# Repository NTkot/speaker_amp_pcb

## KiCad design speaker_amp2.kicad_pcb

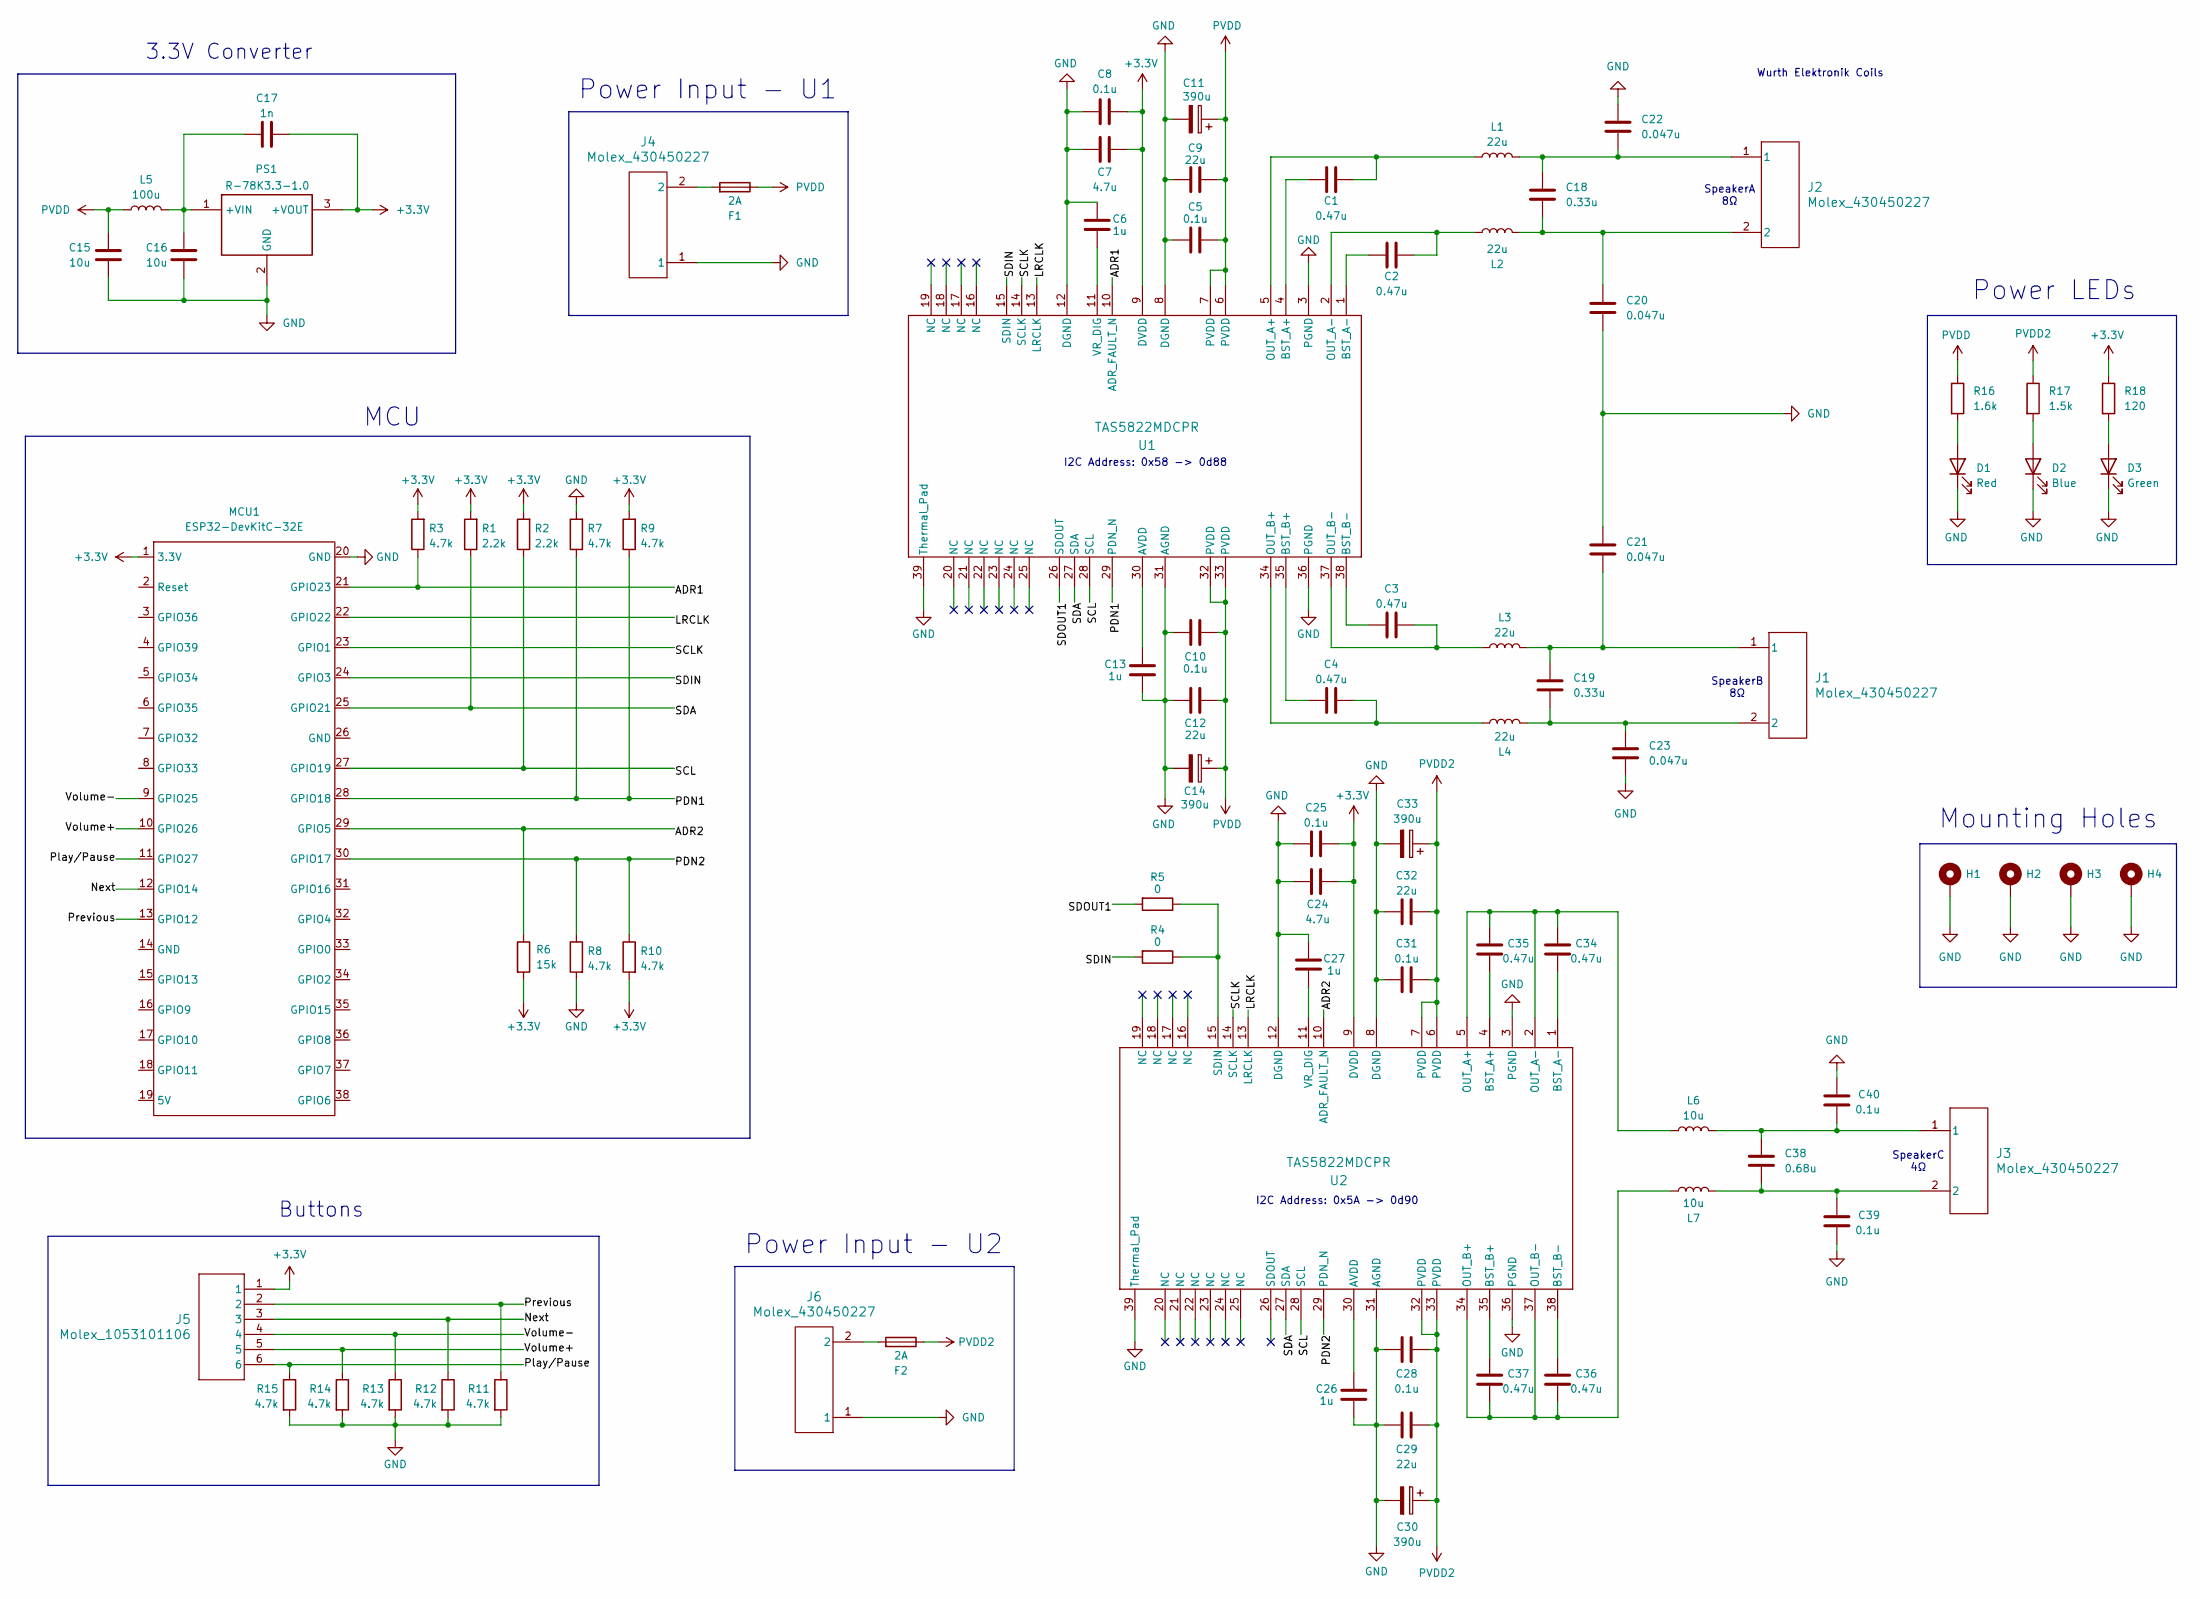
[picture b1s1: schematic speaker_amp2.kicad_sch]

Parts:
C1, C2, C3, C4, C34, C35, C36, C37: 0.47u; C_0603_1608Metric_Pad1.08x0.95mm_HandSolder
C5, C8, C10, C25, C28, C31: 0.1u; C_0603_1608Metric_Pad1.08x0.95mm_HandSolder
C6, C13, C26, C27: 1u; C_0603_1608Metric_Pad1.08x0.95mm_HandSolder
C7, C24: 4.7u; C_0805_2012Metric_Pad1.18x1.45mm_HandSolder
C9, C12, C29, C32: 22u; C_0805_2012Metric_Pad1.18x1.45mm_HandSolder
C11, C14, C30, C33: 390u; CP_Radial_D8.0mm_P3.50mm
C15, C16: 10u; C_0805_2012Metric_Pad1.18x1.45mm_HandSolder
C17: 1n; C_0805_2012Metric_Pad1.18x1.45mm_HandSolder
C18, C19: 0.33u; C_2824
C20, C21, C22, C23: 0.047u; C_2220_5750Metric_Pad1.97x5.40mm_HandSolder
C38: 0.68u; C_2220_5750Metric_Pad1.97x5.40mm_HandSolder
C39, C40: 0.1u; C_2220_5750Metric_Pad1.97x5.40mm_HandSolder
D1: Red; LED_PLCC-2_3.4x3.0mm_KA
D2: Blue; LED_PLCC-2_3.4x3.0mm_KA
D3: Green; LED_PLCC-2_3.4x3.0mm_KA
F1, F2: 2A; Fuse_1206_3216Metric
H1, H2, H3, H4: MountingHole_Pad; MountingHole_3.2mm_M3_DIN965_Pad_TopBottom
J1, J2, J3, J4, J6: Molex_430450227; 430450227_MOLEX
J5: Molex_1053101106
L1, L2, L3, L4: 22u; WE_7447773220
L5: 100u; RLS186
L6, L7: 10u; L_Wuerth_WE-PDF_Handsoldering_7mm_apart
MCU1: ESP32-DevKitC-32E
PS1: R-78K3.3-1.0; R78K3310
R1, R2: 2.2k; R_0805_2012Metric_Pad1.20x1.40mm_HandSolder
R3, R7, R8, R9, R10, R11, R12, R13, R14, R15: 4.7k; R_0805_2012Metric_Pad1.20x1.40mm_HandSolder
R4, R5: 0; R_0805_2012Metric_Pad1.20x1.40mm_HandSolder
R6: 15k; R_0805_2012Metric_Pad1.20x1.40mm_HandSolder
R16: 1.6k; R_0805_2012Metric_Pad1.20x1.40mm_HandSolder
R17: 1.5k; R_0805_2012Metric_Pad1.20x1.40mm_HandSolder
R18: 120; R_0805_2012Metric_Pad1.20x1.40mm_HandSolder
U1, U2: TAS5822MDCPR; DCP0038A-IPC_C

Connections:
+3.3V: C7.1, C8.1, C17.1, C24.2, C25.1, J5.1, MCU1.1 (3.3V), PS1.3 (+VOUT), R1.2, R2.2, R3.2, R6.2, R9.2, R10.2, R18.1, U1.9 (DVDD), U2.9 (DVDD)
/ADR1: MCU1.21 (GPIO23), R3.1, U1.10 (ADR_FAULT_N)
/ADR2: MCU1.29 (GPIO5), R6.1, U2.10 (ADR_FAULT_N)
/LRCLK: MCU1.22 (GPIO22), U1.13 (LRCLK), U2.13 (LRCLK)
/Next: J5.3, MCU1.12 (GPIO14), R12.1
/PDN1: MCU1.28 (GPIO18), R7.1, R9.1, U1.29 (PDN_N)
/PDN2: MCU1.30 (GPIO17), R8.1, R10.1, U2.29 (PDN_N)
/Play/Pause: J5.6, MCU1.11 (GPIO27), R15.1
/Previous: J5.2, MCU1.13 (GPIO12), R11.1
/SCL: MCU1.27 (GPIO19), R2.1, U1.28 (SCL), U2.28 (SCL)
/SCLK: MCU1.23 (GPIO1), U1.14 (SCLK), U2.14 (SCLK)
/SDA: MCU1.25 (GPIO21), R1.1, U1.27 (SDA), U2.27 (SDA)
/SDIN: MCU1.24 (GPIO3), R4.2, U1.15 (SDIN)
/SDOUT1: R5.2, U1.26 (SDOUT)
/Volume+: J5.5, MCU1.10 (GPIO26), R14.1
/Volume-: J5.4, MCU1.9 (GPIO25), R13.1
GND: C5.1, C6.2, C7.2, C8.2, C9.1, C10.1, C11.2, C12.1, C13.1, C14.2, C15.1, C16.1, C20.2, C21.1, C22.1, C23.2, C24.1, C25.2, C26.1, C27.1, C28.2, C29.2, C30.2, C31.2, C32.2, C33.2, C39.1, C40.2, D1.1 (K), D2.1 (K), D3.1 (K), H1.1, H2.1, H3.1, H4.1, J4.1, J6.1, MCU1.20 (GND), PS1.2 (GND), R7.2, R8.2, R11.2, R12.2, R13.2, R14.2, R15.2, U1.3 (PGND), U1.8 (DGND), U1.12 (DGND), U1.31 (AGND), U1.36 (PGND), U1.39 (Thermal_Pad), U2.3 (PGND), U2.8 (DGND), U2.12 (DGND), U2.31 (AGND), U2.36 (PGND), U2.39 (Thermal_Pad)
unnamed: C18.1, C22.2, J2.1, L1.2
unnamed: C18.2, C20.1, J2.2, L2.2
unnamed: C19.1, C21.2, J1.1, L3.2
unnamed: C19.2, C23.1, J1.2, L4.2
unnamed: C38.1, C40.1, J3.1, L6.2
unnamed: C38.2, C39.2, J3.2, L7.2
unnamed: D1.2 (A), R16.2
unnamed: D2.2 (A), R17.2
unnamed: D3.2 (A), R18.2
unnamed: F1.2, J4.2
unnamed: F2.2, J6.2
unnamed: C16.2, C17.2, L5.2, PS1.1 (+VIN)
unnamed: C13.2, U1.30 (AVDD)
unnamed: C1.1, U1.4 (BST_A+)
unnamed: C2.1, U1.1 (BST_A-)
unnamed: C4.1, U1.35 (BST_B+)
unnamed: C3.1, U1.38 (BST_B-)
unnamed: C1.2, L1.1, U1.5 (OUT_A+)
unnamed: C2.2, L2.1, U1.2 (OUT_A-)
unnamed: C4.2, L4.1, U1.34 (OUT_B+)
unnamed: C3.2, L3.1, U1.37 (OUT_B-)
unnamed: C6.1, U1.11 (VR_DIG)
unnamed: C26.2, U2.30 (AVDD)
unnamed: C35.1, U2.4 (BST_A+)
unnamed: C34.1, U2.1 (BST_A-)
unnamed: C37.2, U2.35 (BST_B+)
unnamed: C36.2, U2.38 (BST_B-)
unnamed: C34.2, C35.2, L6.1, U2.2 (OUT_A-), U2.5 (OUT_A+)
unnamed: C36.1, C37.1, L7.1, U2.34 (OUT_B+), U2.37 (OUT_B-)
unnamed: R4.1, R5.1, U2.15 (SDIN)
unnamed: C27.2, U2.11 (VR_DIG)
PVDD: C5.2, C9.2, C10.2, C11.1, C12.2, C14.1, C15.2, F1.1, L5.1, R16.1, U1.6 (PVDD), U1.7 (PVDD), U1.32 (PVDD), U1.33 (PVDD)
PVDD2: C28.1, C29.1, C30.1, C31.1, C32.1, C33.1, F2.1, R17.1, U2.6 (PVDD), U2.7 (PVDD), U2.32 (PVDD), U2.33 (PVDD)

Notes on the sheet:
Wurth Elektronik Coils
Power Input - U2
MCU
SpeakerC 4Ω
SpeakerA 8Ω
I2C Address: 0x58 -> 0d88
I2C Address: 0x5A -> 0d90
Power LEDs
SpeakerB 8Ω
Buttons
Mounting Holes
3.3V Converter
Power Input - U1

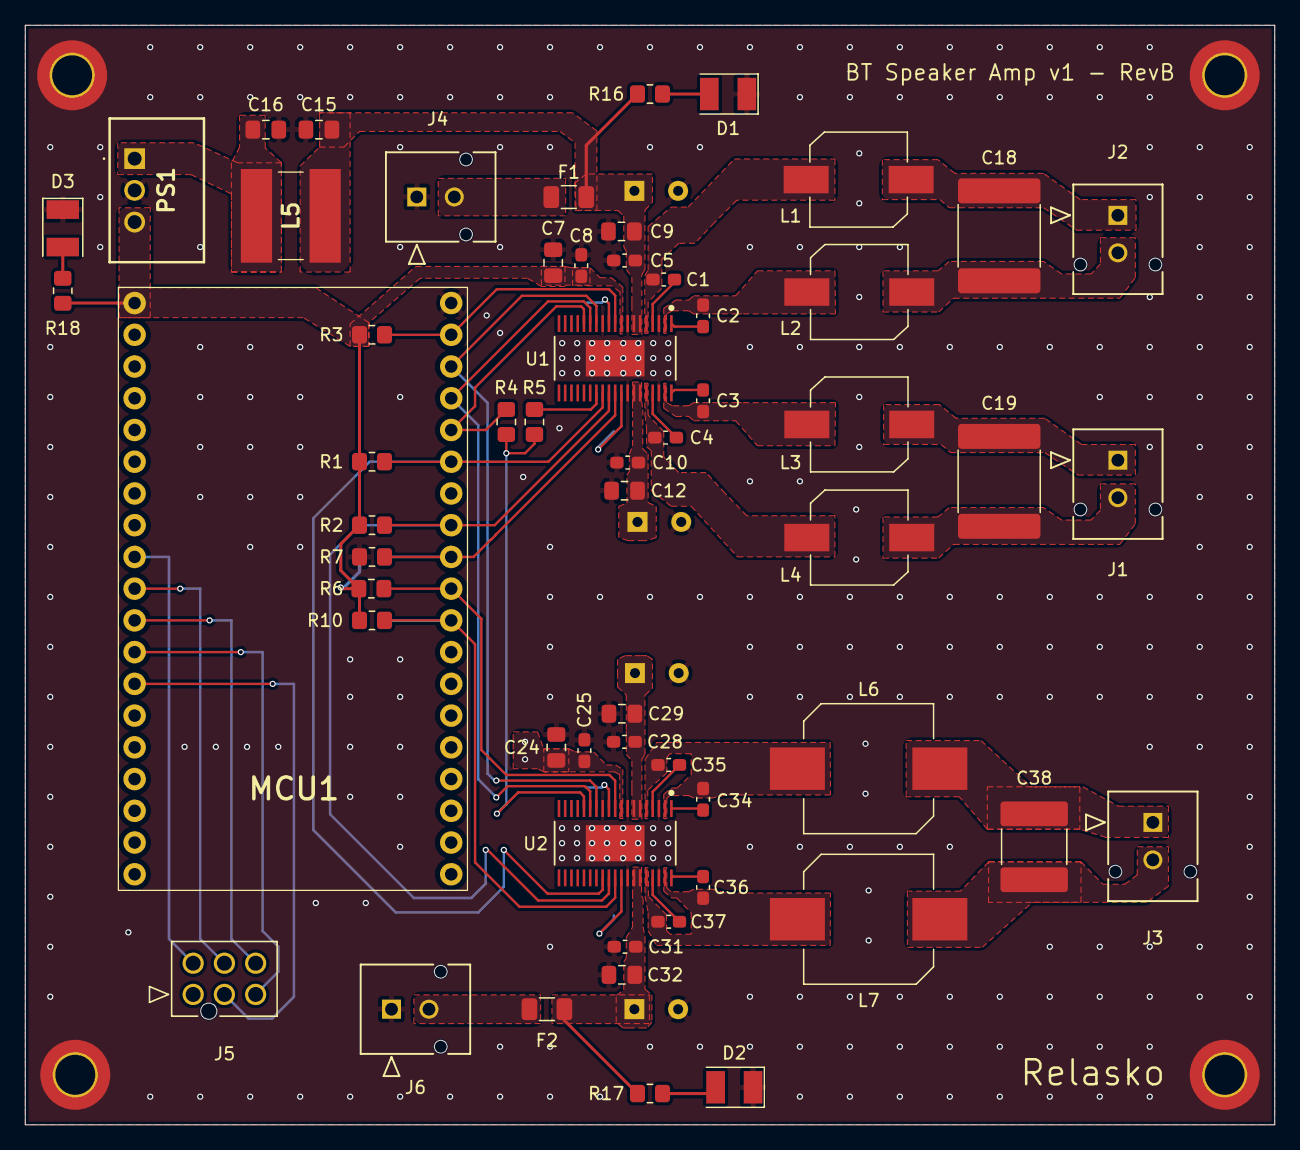
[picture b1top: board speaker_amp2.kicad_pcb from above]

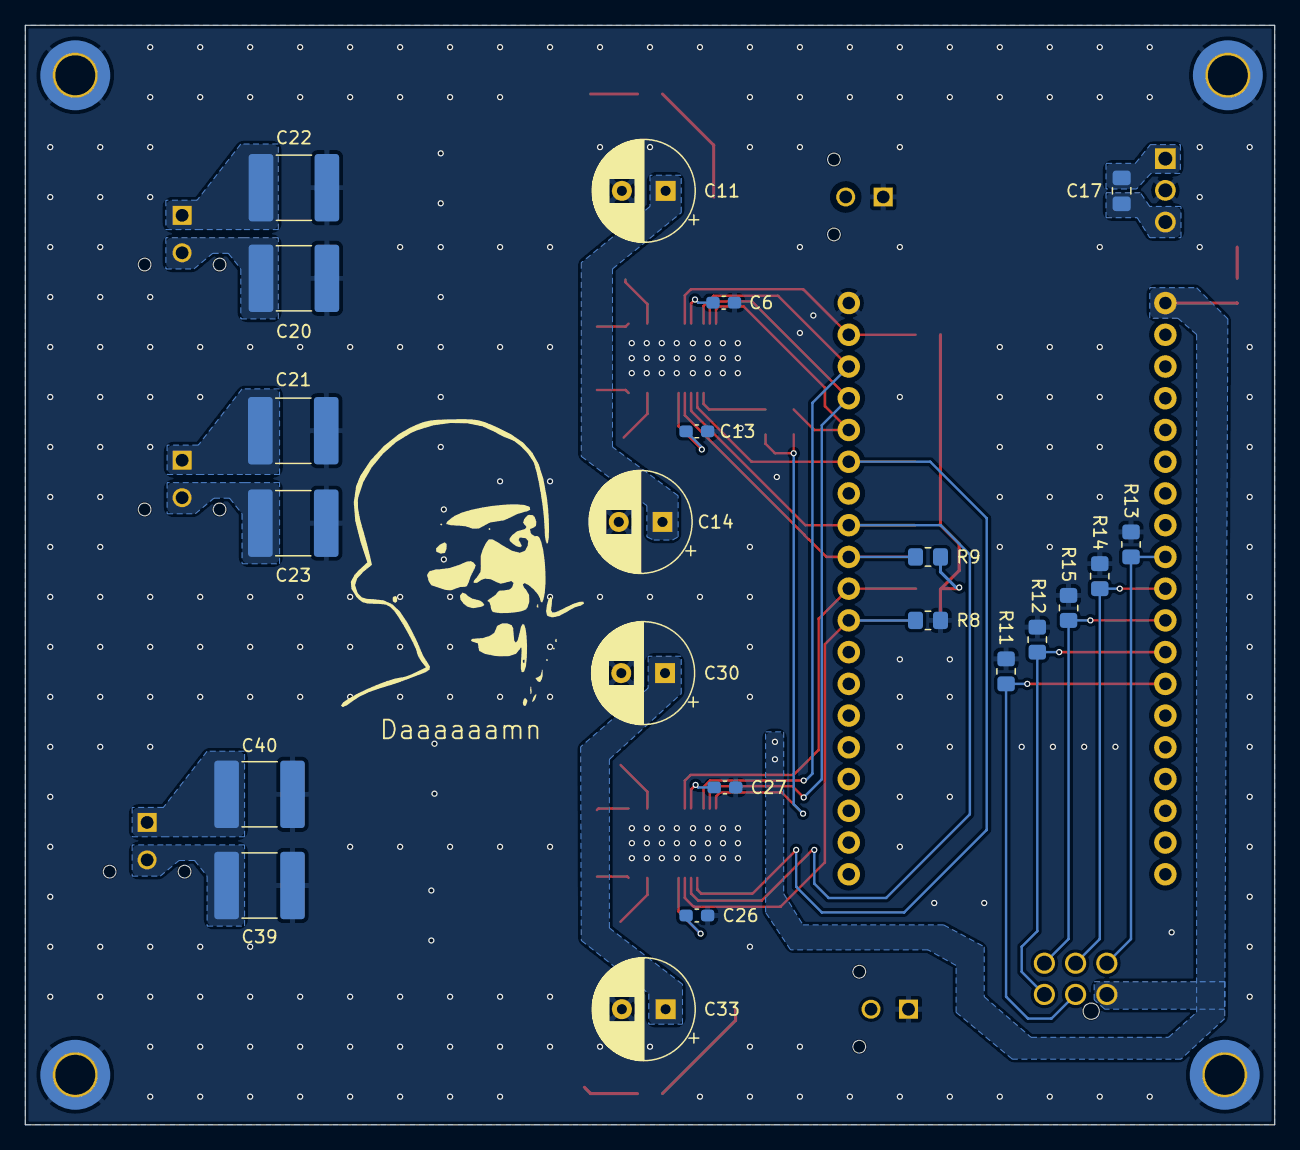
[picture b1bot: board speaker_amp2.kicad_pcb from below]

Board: 2 copper layers, 100.0 x 88.0 mm, 84 parts (22 on the bottom side), 50 nets.

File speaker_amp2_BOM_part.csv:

"Reference","Value","Qty","MouserLink", "MouserPart"
"C1,C2,C3,C4,C34,C35,C36,C37","0.47u","8","https://gr.mouser.com/ProductDetail/TAIYO-YUDEN/MLASU168SB74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", "963-MLASU168SB7474KT"
"C5,C8,C10,C25,C28,C31","0.1u","6","https://gr.mouser.com/ProductDetail/KEMET/C0603C104J5RACTM?q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", "80-C0603C104J5RACTM"
"C6,C13,C26,C27","1u","4","https://gr.mouser.com/ProductDetail/TAIYO-YUDEN/MLAST168SB71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", "963-MLAST168SB7105KT"
"C7,C24","4.7u","2","https://gr.mouser.com/ProductDetail/Murata-Electronics/GRM21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", "81-GRM21BZ7YA475KE5L"
"C9,C12,C29,C32","22u","4","https://gr.mouser.com/ProductDetail/TDK/C2012X5R1V226M125AC?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", "810-C2012X5R1V226MAC"
"C11,C14,C30,C33","390u","4","https://gr.mouser.com/ProductDetail/Panasonic/EEU-FR1V391L?q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", "667-EEU-FR1V391L"
"C15,C16","10u","2","https://gr.mouser.com/ProductDetail/KYOCERA-AVX/KGM21AR71C10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", "581-KGM21AR71C106MU"
"C17","1n","1","https://gr.mouser.com/ProductDetail/Samsung-Electro-Mechanic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", "187-CL21B102JCANNNC"
"C18,C19","0.33u","2","https://gr.mouser.com/ProductDetail/WIMA/SMD2824-.33-100-10T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", "505-SMD2824.3310010T"
"C20,C21,C22,C23","0.047u","4","https://gr.mouser.com/ProductDetail/WIMA/SMDTD02470QA00KP00?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", "505-SMDTD02470QAKP00"
"C38","0.68u","1","https://gr.mouser.com/ProductDetail/WIMA/SMDIC03680TB00KQ00?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", "505-PPS28.68/63/10"
"C39,C40","0.1u","2","https://gr.mouser.com/ProductDetail/WIMA/SMDTD03100QA00KP00?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", " 505-SMDTD03100QAKP00"
"D1","Red","1","https://gr.mouser.com/ProductDetail/Vishay-Semiconductors/VL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", "78-VLMK3102"
"D2","Blue","1","https://gr.mouser.com/ProductDetail/Vishay-Semiconductors/VL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", "78-VLMB41P1Q2-GS18"
"D3","Green","1","https://gr.mouser.com/ProductDetail/Vishay-Semiconductors/VL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", "78-VLMG31L1M2-GS18"
"F1,F2","2A","2","https://gr.mouser.com/ProductDetail/Bel-Fuse/0685P2000-01?qs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", "530-0685P2000-01"
"J1,J2,J3,J4,J6","Molex_430450227","5","https://gr.mouser.com/ProductDetail/Molex/43045-0227?qs=R7%2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", "538-43045-0227"
"J5","Molex_1053101106","1","https://gr.mouser.com/ProductDetail/Molex/105310-1106?qs=PqF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", "538-105310-1106"
"L1,L2,L3,L4","22u","4","https://gr.mouser.com/ProductDetail/Wurth-Elektronik/7447773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", "710-7447773220"
"L5","100u","1","https://gr.mouser.com/ProductDetail/RECOM-Power/RLS-186?qs=g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", "919-RLS-186"
"L6,L7","10u","2","https://gr.mouser.com/ProductDetail/Wurth-Elektronik/7447714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", "710-7447714100"
"MCU1","ESP32-DevKitC-32E","1","https://gr.mouser.com/ProductDetail/Espressif-Systems/ESP32-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", "356-ESP32-DEVKITC32E"
"PS1","R-78K3.3-1.0","1","https://gr.mouser.com/ProductDetail/RECOM-Power/R-78K3.3-1.0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", "919-R-78K3.3-1.0"
"R1,R2","2.2k","2","https://gr.mouser.com/ProductDetail/YAGEO/RT0805FRE132K2L?qs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", "603-RT0805FRE132K2L"
"R3,R7,R8,R9,R10,R11,R12,R13,R14,R15","4.7k","10","https://gr.mouser.com/ProductDetail/YAGEO/RT0805DRD074K7L?qs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", "603-RT0805DRD074K7L"
"R4,R5","0","2","https://gr.mouser.com/ProductDetail/Vishay-Beyschlag/MCU0805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", "594-MCU0805MZ0000ZP5"
"R6","15k","1","https://gr.mouser.com/ProductDetail/YAGEO/RT0805DRD0715KL?qs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", "603-RT0805DRD0715KL"
"R16","1.6k","1","https://gr.mouser.com/ProductDetail/KOA-Speer/RK73B2ATTD162J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", "660-RK73B2ATTD162J"
"R17","1.5k","1","https://gr.mouser.com/ProductDetail/KOA-Speer/RK73B2ATTDD152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", "660-RK73B2ATTDD152J"
"R18","120","1","https://gr.mouser.com/ProductDetail/KOA-Speer/RK73B2ATTD121G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", "660-RK73B2ATTD121G"
"U1,U2","TAS5822MDCPR","2","https://gr.mouser.com/ProductDetail/Texas-Instruments/TAS582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", "595-TAS5822MDCPR"

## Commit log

2024-09-23 refactored repo
2024-09-23 added mcu to schematic
2024-09-24 added class D amp and datasheets, added most capacitors to schematic
2024-09-25 added dcdc converter
2024-09-26 finalized logic level dcdc converter
2024-10-05 added new ESP32 footprint lib
2024-10-05 replaced ESP32-C6 with ESP32-WROOM-32E
2024-10-06 added communication wires with amp
2024-10-06 lc filter design work
2024-10-08 fixed scripts
2024-10-09 added C_BTL capacitor
2024-10-09 added C_g cap
2024-10-12 added TAS5733L amp to lib
2024-10-13 added 2nd TAS5822M
2024-10-15 added mono ch bootstrap caps
2024-10-16 finished first iteration, connectors wip
2024-10-19 added connectors
2024-10-20 changes after reviewing schematic
2024-12-01 added button connector
2024-12-01 fixed silkscreen on connector footprints
2024-12-03 finished schematic with speaker buttons
2024-12-05 added button connector to pcb
2024-12-05 placed 3.3V to pcb
2024-12-16 changed amplifiers in schematic to match PCB pins
2024-12-20 placed amp ics, did low-voltage connections
2025-01-12 changed some components (coils) for smaller ones
2025-01-14 changed output capacitors to smaller ones
2025-01-14 finalized pcb component placement; started connections
2025-01-17 started working on subwoofer amp traces
2025-01-18 first finalized pcb
2025-01-21 added LEDs and mounting holes
2025-01-21 preparing heat vias for amps
2025-01-21 Added array of thermal reliefs
2025-01-26 final design + BoM
2025-02-26 final design, sent for production
2025-03-04 added esp32 program to find addresses
2025-03-05 i2c addresses clarification
2025-05-23 removed pcb order files
2025-05-23 removed unnecessary files
2025-05-24 simplified arduino sketches
2025-05-24 added basic bt test sketch for esp32
2025-06-02 update to docs
